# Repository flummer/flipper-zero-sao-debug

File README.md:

# Badgelife SAO Debug Tool for Flipper Zero

This is a relatively simple expansion board for the Flipper Zero, that has the proper connectors to attach SAOs and communicate with the SAO via I2C and the GPIO pins.

It can also be used to communicate with a badge, essentially making the Flipper Zero into an SAO, electrically, which could be usefull for debugging or developing communication between badge as SAOs.

## Designed in KiCad v8.99 (nightly)

To open the project, you will need to install a recent nightly build (og v9 or newer when released), KiCad v8 or earlier won't open this design directly.

## License

The hardware design of the `main` branch of this repository is released under the following license:

* the "Creative Commons Attribution-ShareAlike 4.0 International License"
  (CC BY-SA 4.0) full text of this license is included in the LICENSE file
  and a copy can also be found at
  [http://creativecommons.org/licenses/by-sa/4.0/](http://creativecommons.org/licenses/by-sa/4.0/)

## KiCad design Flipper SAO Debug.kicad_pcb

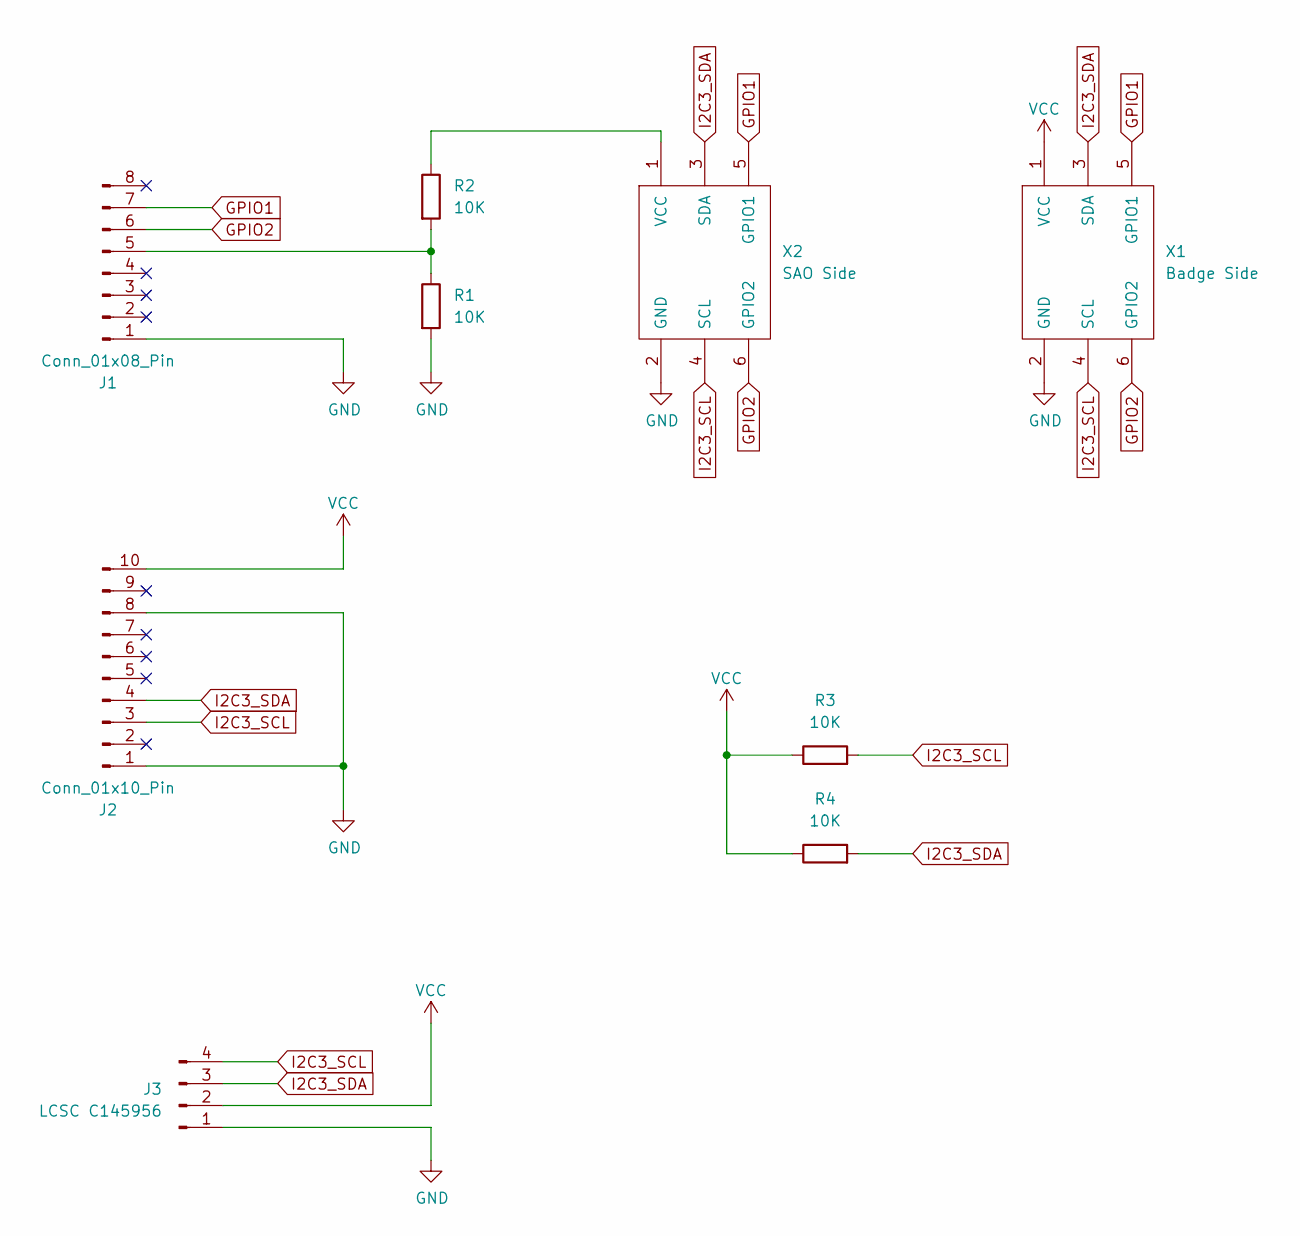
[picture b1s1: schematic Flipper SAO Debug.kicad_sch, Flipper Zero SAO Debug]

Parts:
J1: Conn_01x08_Pin; PinHeader_1x08_P2.54mm_Horizontal
J2: Conn_01x10_Pin; PinHeader_1x10_P2.54mm_Horizontal
J3: LCSC C145956; JST_SH_SM04B-SRSS-TB_1x04-1MP_P1.00mm_Horizontal
R1, R2, R3, R4: 10K; R_0603_1608Metric
X1: Badge Side; Badgelife-SAOv169-BADGE-2x3
X2: SAO Side; Badgelife-SAOv169-SAO-2x3

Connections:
GND: J1.1, J2.1, J2.8, J3.1, R1.2, X1.2 (GND), X2.2 (GND)
GPIO1: J1.7, X1.5 (GPIO1), X2.5 (GPIO1)
GPIO2: J1.6, X1.6 (GPIO2), X2.6 (GPIO2)
I2C3_SCL: J2.3, J3.4, R3.2, X1.4 (SCL), X2.4 (SCL)
I2C3_SDA: J2.4, J3.3, R4.2, X1.3 (SDA), X2.3 (SDA)
unnamed: J1.5, R1.1, R2.2
unnamed: R2.1, X2.1 (VCC)
VCC: J2.10, J3.2, R3.1, R4.1, X1.1 (VCC)

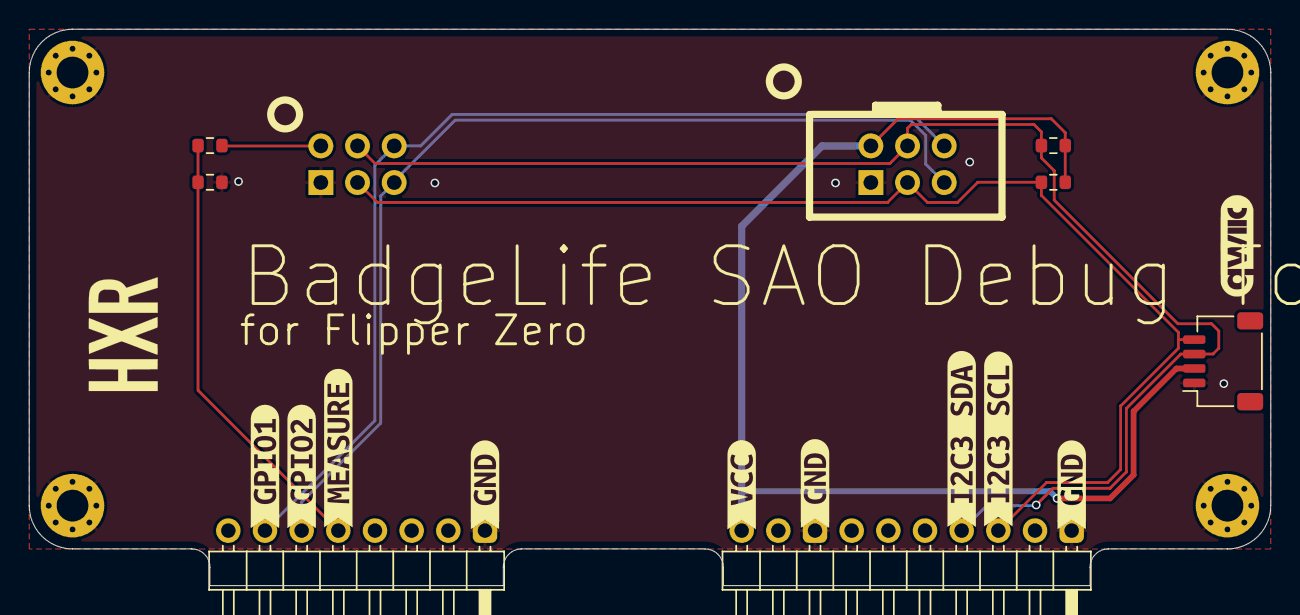
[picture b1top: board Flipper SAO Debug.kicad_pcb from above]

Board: 2 copper layers, 86.0 x 38.5 mm, 18 parts (0 on the bottom side), 8 nets.

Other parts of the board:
kibuzzard-67014A6A: G***; kibuzzard-67014A6A
kibuzzard-670147AD: G***; kibuzzard-670147AD
kibuzzard-670147DA: G***; kibuzzard-670147DA
kibuzzard-670147E8: G***; kibuzzard-670147E8
kibuzzard-670147FB: G***; kibuzzard-670147FB
kibuzzard-6701479F: G***; kibuzzard-6701479F
kibuzzard-67014762, kibuzzard-67014762#2, kibuzzard-67014762#3: G***; kibuzzard-67014762
